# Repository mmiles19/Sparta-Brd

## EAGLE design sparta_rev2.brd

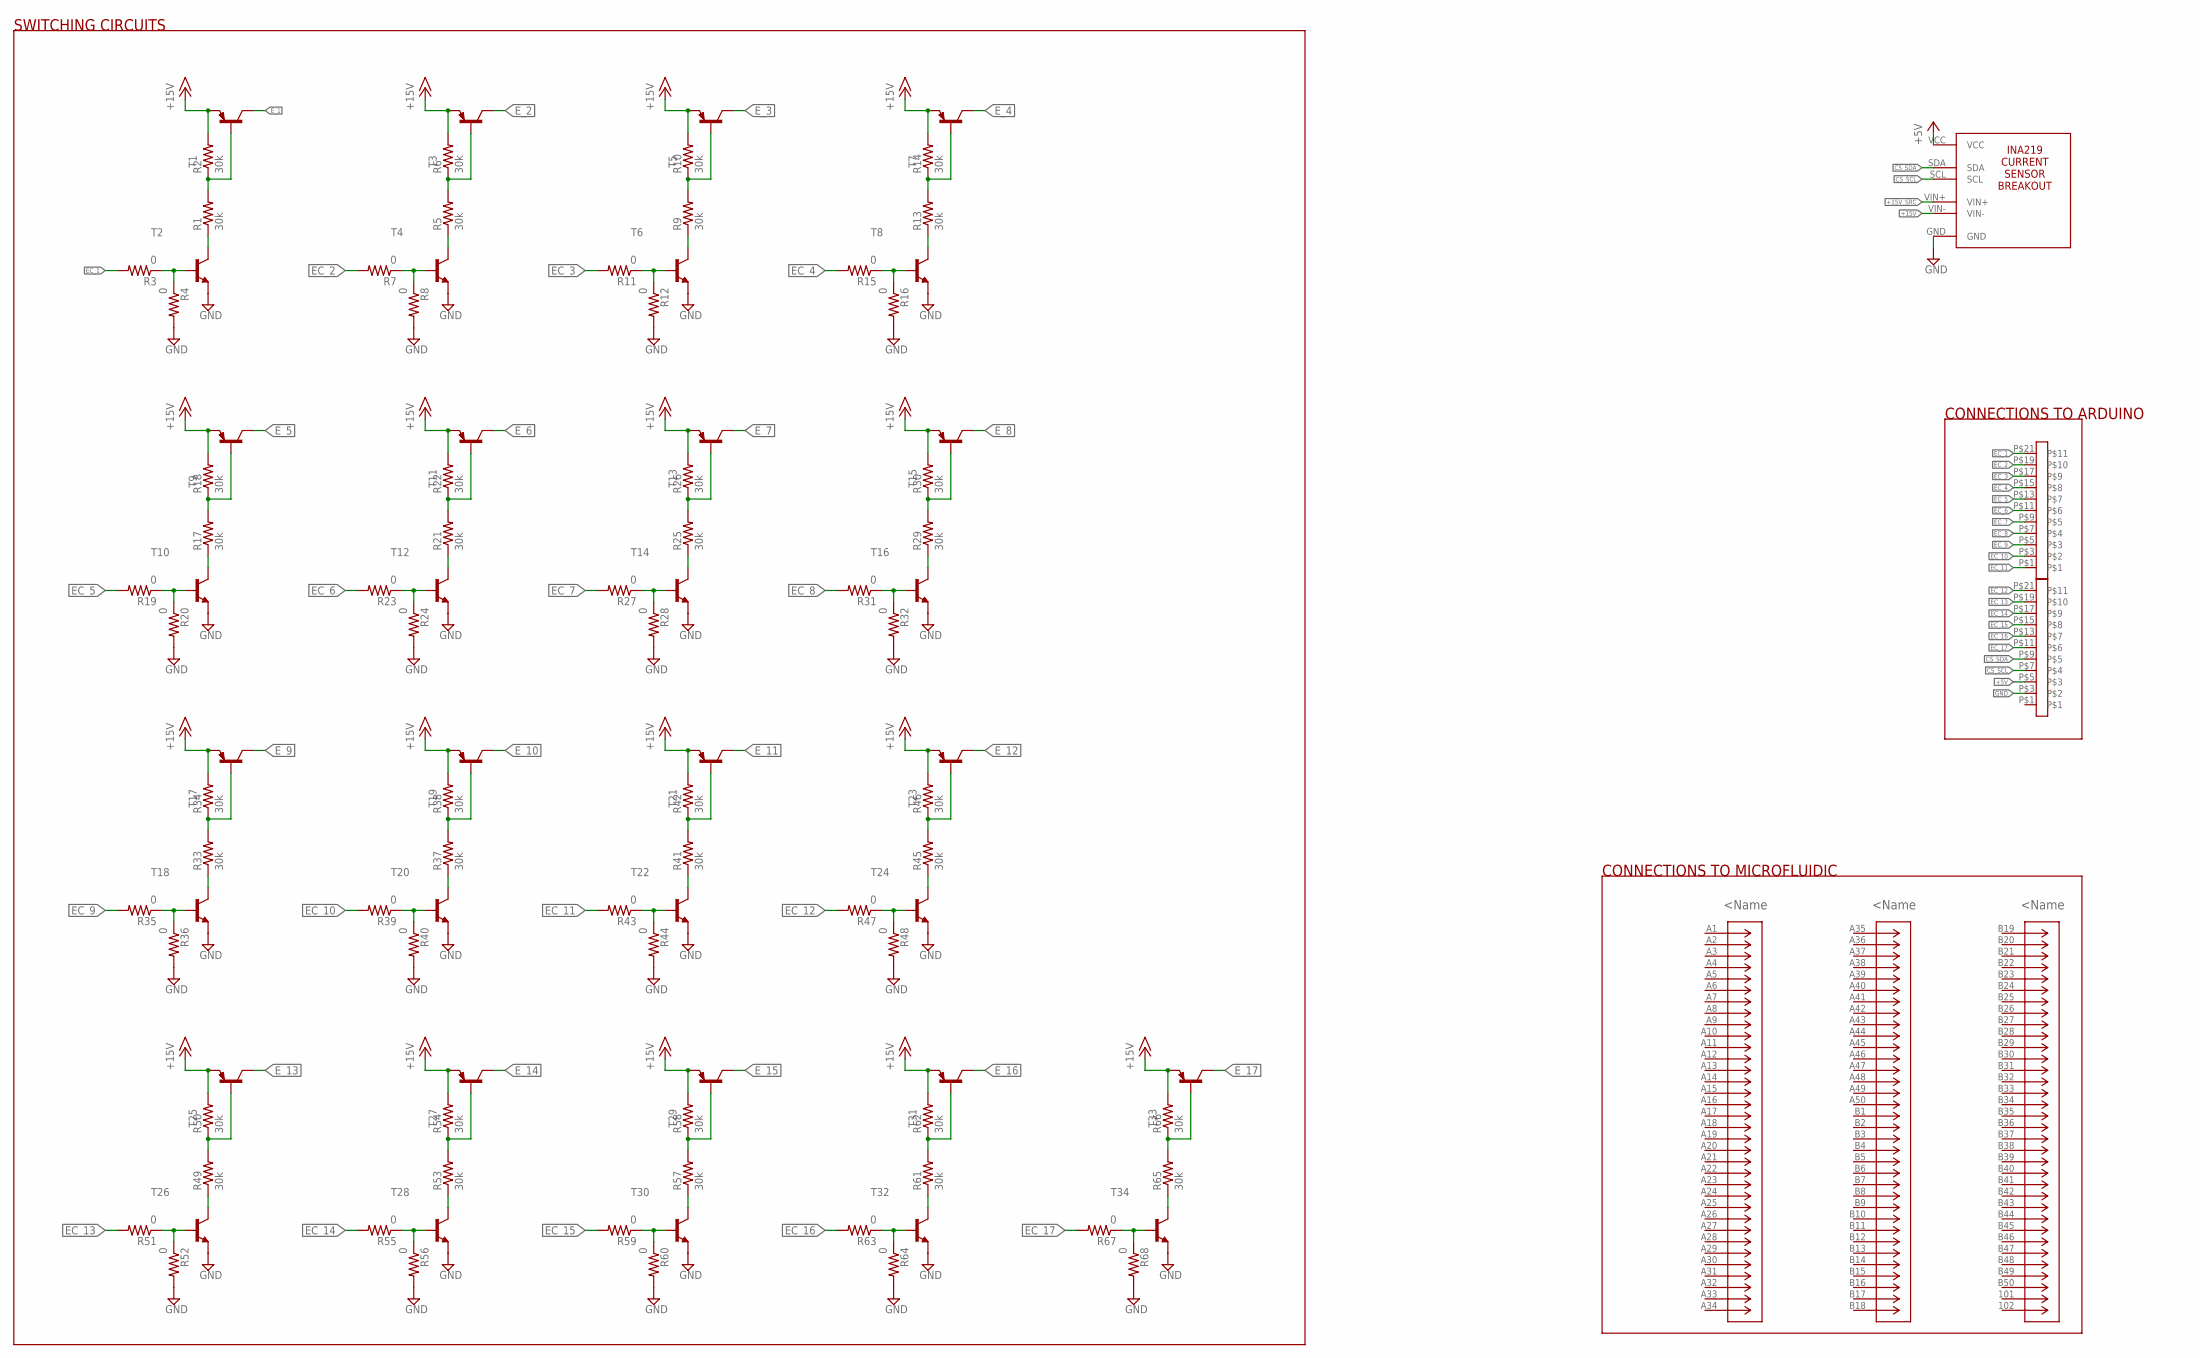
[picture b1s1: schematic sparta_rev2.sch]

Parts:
J1: FX2-100P-1.27SV(71); CON100_2X50_UTZF_FX2C
R1, R2, R5, R6, R9, R10, R13, R14, R17, R18, R21, R22, R25, R26, R29, R30, R33, R34, R37, R38, R41, R42, R45, R46, R49, R50, R53, R54, R57, R58, R61, R62, R65, R66: 30k; 0207/10
R3, R4, R7, R8, R11, R12, R15, R16, R19, R20, R23, R24, R27, R28, R31, R32, R35, R36, R39, R40, R43, R44, R47, R48, R51, R52, R55, R56, R59, R60, R63, R64, R67, R68: 0; 0207/10
T1, T3, T5, T7, T9, T11, T13, T15, T17, T19, T21, T23, T25, T27, T29, T31, T33: -PNP-TO220V; TO220V
T2, T4, T6, T8, T10, T12, T14, T16, T18, T20, T22, T24, T26, T28, T30, T32, T34: -NPN-TO92-EBC; TO92-EBC
U$1: INA219_SIL
U$2, U$3: HEADERS_11

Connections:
+5V: U$1.VCC
+15V: R2.2, R6.2, R10.2, R14.2, R18.2, R22.2, R26.2, R30.2, R34.2, R38.2, R42.2, R46.2, R50.2, R54.2, R58.2, R62.2, R66.2, T1.3 (E), T3.3 (E), T5.3 (E), T7.3 (E), T9.3 (E), T11.3 (E), T13.3 (E), T15.3 (E), T17.3 (E), T19.3 (E), T21.3 (E), T23.3 (E), T25.3 (E), T27.3 (E), T29.3 (E), T31.3 (E), T33.3 (E), U$1.VIN-
+15V_SRC: U$1.VIN+
CS_SCL: U$1.SCL
CS_SDA: U$1.SDA
EC_1: R3.2, U$2.P$21
EC_2: R7.2
EC_3: R11.2
EC_4: R15.2
EC_5: R19.2
EC_6: R23.2
EC_7: R27.2
EC_8: R31.2
EC_9: R35.2
EC_10: R39.2
EC_11: R43.2
EC_12: R47.2
EC_13: R51.2
EC_14: R55.2
EC_15: R59.2
EC_16: R63.2
EC_17: R67.2
E_1: T1.2 (C)
E_2: T3.2 (C)
E_3: T5.2 (C)
E_4: T7.2 (C)
E_5: T9.2 (C)
E_6: T11.2 (C)
E_7: T13.2 (C)
E_8: T15.2 (C)
E_9: T17.2 (C)
E_10: T19.2 (C)
E_11: T21.2 (C)
E_12: T23.2 (C)
E_13: T25.2 (C)
E_14: T27.2 (C)
E_15: T29.2 (C)
E_16: T31.2 (C)
E_17: T33.2 (C)
GND: R4.2, R8.2, R12.2, R16.2, R20.2, R24.2, R28.2, R32.2, R36.2, R40.2, R44.2, R48.2, R52.2, R56.2, R60.2, R64.2, R68.2, T2.E, T4.E, T6.E, T8.E, T10.E, T12.E, T14.E, T16.E, T18.E, T20.E, T22.E, T24.E, T26.E, T28.E, T30.E, T32.E, T34.E, U$1.GND
unnamed: R3.1, R4.1, T2.B
unnamed: R1.1, T2.C
unnamed: R1.2, R2.1, T1.1 (B)
unnamed: R7.1, R8.1, T4.B
unnamed: R5.1, T4.C
unnamed: R5.2, R6.1, T3.1 (B)
unnamed: R11.1, R12.1, T6.B
unnamed: R9.1, T6.C
unnamed: R9.2, R10.1, T5.1 (B)
unnamed: R15.1, R16.1, T8.B
unnamed: R13.1, T8.C
unnamed: R13.2, R14.1, T7.1 (B)
unnamed: R19.1, R20.1, T10.B
unnamed: R17.1, T10.C
unnamed: R17.2, R18.1, T9.1 (B)
unnamed: R23.1, R24.1, T12.B
unnamed: R21.1, T12.C
unnamed: R21.2, R22.1, T11.1 (B)
unnamed: R27.1, R28.1, T14.B
unnamed: R25.1, T14.C
unnamed: R25.2, R26.1, T13.1 (B)
unnamed: R31.1, R32.1, T16.B
unnamed: R29.1, T16.C
unnamed: R29.2, R30.1, T15.1 (B)
unnamed: R35.1, R36.1, T18.B
unnamed: R33.1, T18.C
unnamed: R33.2, R34.1, T17.1 (B)
unnamed: R39.1, R40.1, T20.B
unnamed: R37.1, T20.C
unnamed: R37.2, R38.1, T19.1 (B)
unnamed: R43.1, R44.1, T22.B
unnamed: R41.1, T22.C
unnamed: R41.2, R42.1, T21.1 (B)
unnamed: R47.1, R48.1, T24.B
unnamed: R45.1, T24.C
unnamed: R45.2, R46.1, T23.1 (B)
unnamed: R51.1, R52.1, T26.B
unnamed: R49.1, T26.C
unnamed: R49.2, R50.1, T25.1 (B)
unnamed: R55.1, R56.1, T28.B
unnamed: R53.1, T28.C
unnamed: R53.2, R54.1, T27.1 (B)
unnamed: R59.1, R60.1, T30.B
unnamed: R57.1, T30.C
unnamed: R57.2, R58.1, T29.1 (B)
unnamed: R63.1, R64.1, T32.B
unnamed: R61.1, T32.C
unnamed: R61.2, R62.1, T31.1 (B)
unnamed: R67.1, R68.1, T34.B
unnamed: R65.1, T34.C
unnamed: R65.2, R66.1, T33.1 (B)

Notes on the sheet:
SWITCHING CIRCUITS
CONNECTIONS TO ARDUINO
CONNECTIONS TO MICROFLUIDIC

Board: 2 copper layers, 106 parts (0 on the bottom side), 54 nets, no tracks yet.

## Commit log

2017-02-09 :space_invader: Added .gitattributes & .gitignore files
2017-02-09 new sparta brd, majority of sch done, starting brd
    need to complete connections to microfluidic in sch
